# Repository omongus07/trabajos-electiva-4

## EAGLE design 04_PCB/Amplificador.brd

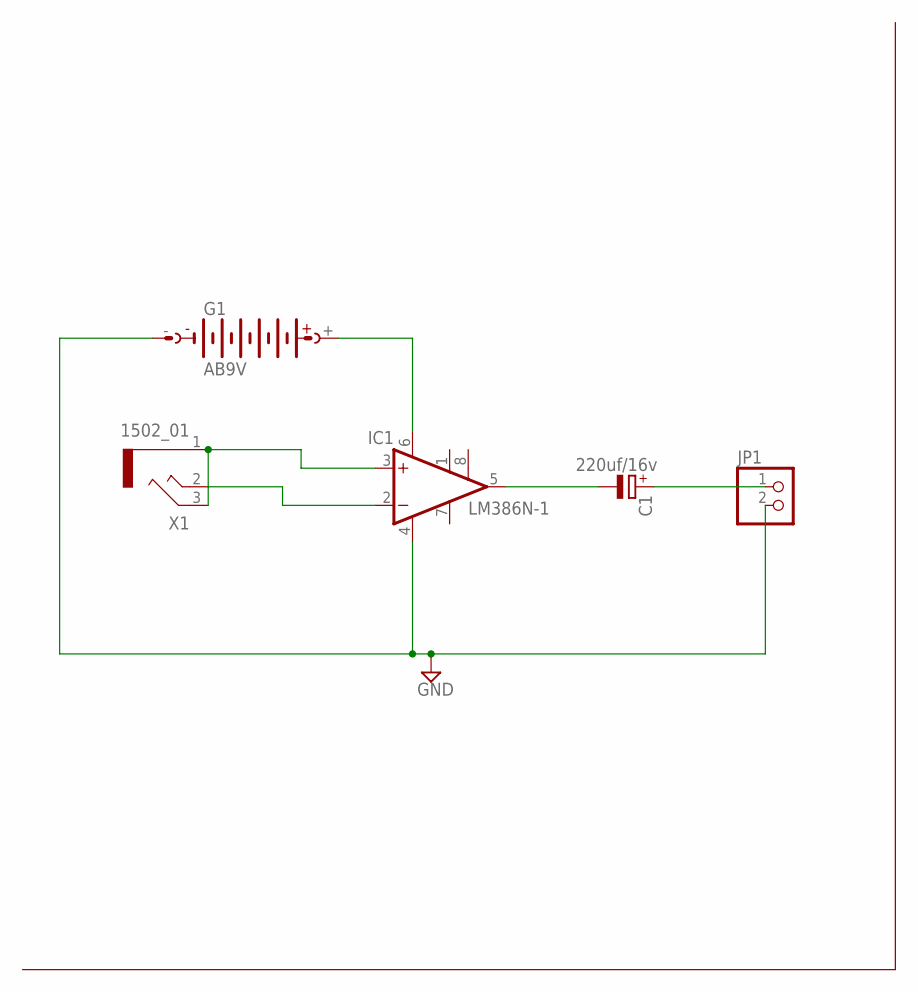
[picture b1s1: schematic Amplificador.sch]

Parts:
C1: 220uf/16v; E3,5-8
G1: AB9V
IC1: LM386N-1; DIL08
JP1: PINHD-1X2; 1X02
X1: 1502_01

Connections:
GND: G1.-, IC1.4 (GND), JP1.2
unnamed: IC1.2 (-IN), X1.2 (3)
unnamed: IC1.3 (+IN), X1.1, X1.3 (2)
unnamed: G1.+, IC1.6 (VS)
unnamed: C1.-, IC1.5 (OUT)
unnamed: C1.+, JP1.1

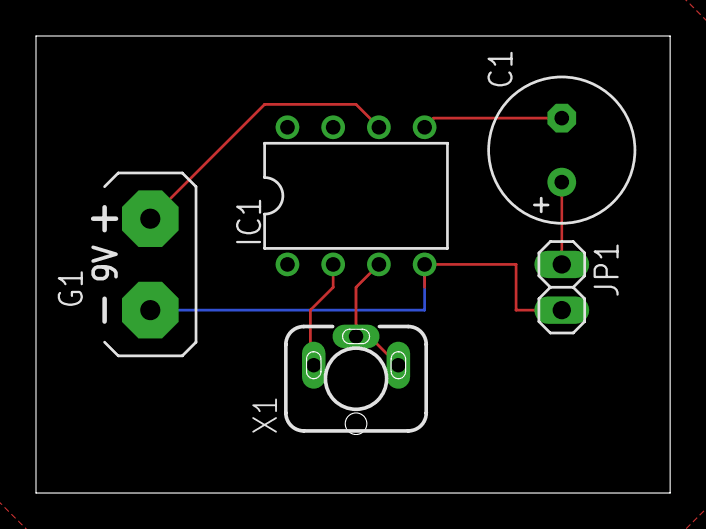
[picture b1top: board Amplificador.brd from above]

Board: 2 copper layers, 35.2 x 25.4 mm, 5 parts (0 on the bottom side), 6 nets.
